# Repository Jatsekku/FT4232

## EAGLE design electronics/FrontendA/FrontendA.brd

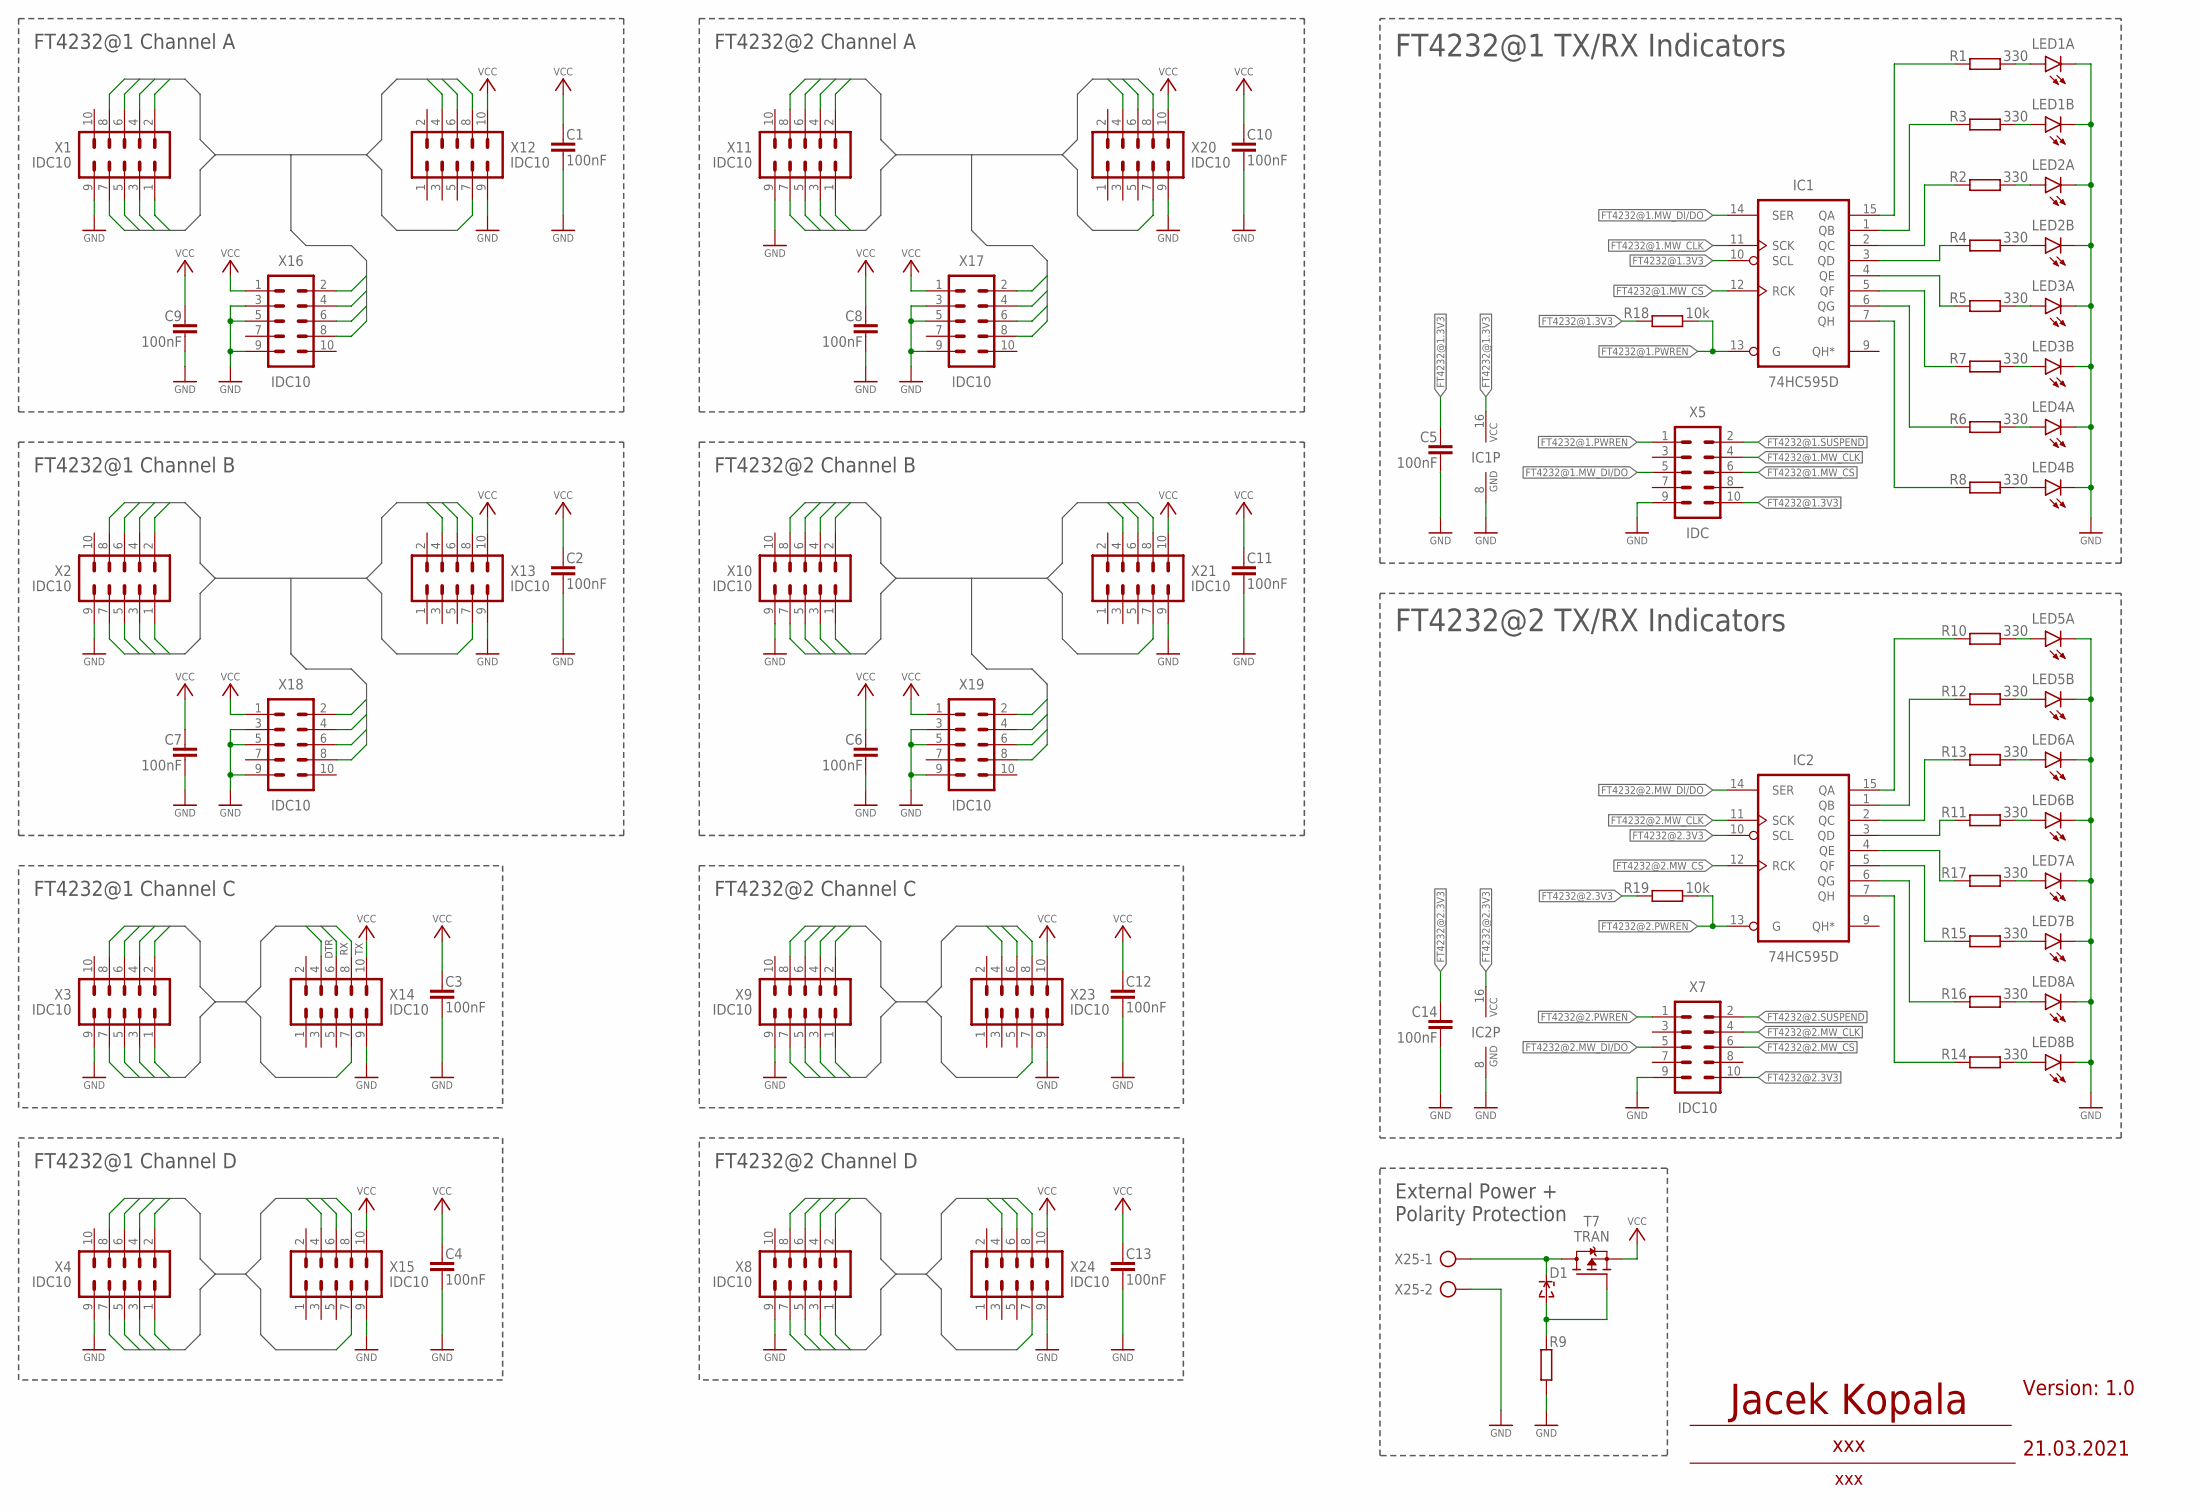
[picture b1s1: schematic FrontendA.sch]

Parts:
C1, C2, C3, C4, C5, C6, C7, C8, C9, C10, C11, C12, C13, C14: 100nF; C0805
D1: ZENERSOD-323F; SOD-323F
IC1, IC2: 74HC595D; SO16
LED1, LED2, LED3, LED4, LED5, LED6, LED7, LED8: LSG-T676; WL-SFCW-0603
R1, R2, R3, R4, R5, R6, R7, R8, R10, R11, R12, R13, R14, R15, R16, R17: 330; R0805
R9: R-EU_R0805; R0805
R18, R19: 10k; R0805
T7: TRAN; TO252
X1, X2, X3, X4, X7, X8, X9, X10, X11: IDC10; MA05-2
X5: IDC; MA05-2
X12, X13, X14, X15, X16, X17, X18, X19, X20, X21, X23, X24: IDC10; ML10
X25: AK500/2

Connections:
FT4232@1.3V3: C5.1, IC1.10 (SCL), IC1.16 (VCC), R18.2, X5.10
FT4232@1.AD0: X1.1, X12.8, X16.4
FT4232@1.AD1: X1.2, X12.6, X16.8
FT4232@1.AD2: X1.3, X12.7, X16.6
FT4232@1.AD3: X1.4, X16.2
FT4232@1.AD4: X1.5, X12.4
FT4232@1.AD5: X1.6
FT4232@1.AD6: X1.7
FT4232@1.AD7: X1.8
FT4232@1.BD0: X2.1, X13.8, X18.4
FT4232@1.BD1: X2.2, X13.6, X18.8
FT4232@1.BD2: X2.3, X13.7, X18.6
FT4232@1.BD3: X2.4, X18.2
FT4232@1.BD4: X2.5, X13.4
FT4232@1.BD5: X2.6
FT4232@1.BD6: X2.7
FT4232@1.BD7: X2.8
FT4232@1.CD0: X3.1, X14.8
FT4232@1.CD1: X3.2, X14.6
FT4232@1.CD2: X3.3, X14.7
FT4232@1.CD3: X3.4
FT4232@1.CD4: X3.5, X14.4
FT4232@1.CD5: X3.6
FT4232@1.CD6: X3.7
FT4232@1.CD7: X3.8
FT4232@1.DD0: X4.1, X15.8
FT4232@1.DD1: X4.2, X15.6
FT4232@1.DD2: X4.3, X15.7
FT4232@1.DD3: X4.4
FT4232@1.DD4: X4.5, X15.4
FT4232@1.DD5: X4.6
FT4232@1.DD6: X4.7
FT4232@1.DD7: X4.8
FT4232@1.MW_CLK: IC1.11 (SCK), X5.4
FT4232@1.MW_CS: IC1.12 (RCK), X5.6
FT4232@1.MW_DI/DO: IC1.14 (SER), X5.5
FT4232@1.PWREN: IC1.13 (G), R18.1, X5.1
FT4232@1.SUSPEND: X5.2
FT4232@2.3V3: C14.1, IC2.10 (SCL), IC2.16 (VCC), R19.2, X7.10
FT4232@2.AD0: X11.1, X17.4, X20.8
FT4232@2.AD1: X11.2, X17.8, X20.6
FT4232@2.AD2: X11.3, X17.6, X20.7
FT4232@2.AD3: X11.4, X17.2
FT4232@2.AD4: X11.5, X20.4
FT4232@2.AD5: X11.6
FT4232@2.AD6: X11.7
FT4232@2.AD7: X11.8
FT4232@2.BD0: X10.1, X19.4, X21.8
FT4232@2.BD1: X10.2, X19.8, X21.6
FT4232@2.BD2: X10.3, X19.6, X21.7
FT4232@2.BD3: X10.4, X19.2
FT4232@2.BD4: X10.5, X21.4
FT4232@2.BD5: X10.6
FT4232@2.BD6: X10.7
FT4232@2.BD7: X10.8
FT4232@2.CD0: X9.1, X23.8
FT4232@2.CD1: X9.2, X23.6
FT4232@2.CD2: X9.3, X23.7
FT4232@2.CD3: X9.4
FT4232@2.CD4: X9.5, X23.4
FT4232@2.CD5: X9.6
FT4232@2.CD6: X9.7
FT4232@2.CD7: X9.8
FT4232@2.DD0: X8.1, X24.8
FT4232@2.DD1: X8.2, X24.6
FT4232@2.DD2: X8.3, X24.7
FT4232@2.DD3: X8.4
FT4232@2.DD4: X8.5, X24.4
FT4232@2.DD5: X8.6
FT4232@2.DD6: X8.7
FT4232@2.DD7: X8.8
FT4232@2.MW_CLK: IC2.11 (SCK), X7.4
FT4232@2.MW_CS: IC2.12 (RCK), X7.6
FT4232@2.MW_DI/DO: IC2.14 (SER), X7.5
FT4232@2.PWREN: IC2.13 (G), R19.1, X7.1
FT4232@2.SUSPEND: X7.2
GND: C1.2, C2.2, C3.2, C4.2, C5.2, C6.2, C7.2, C8.2, C9.2, C10.2, C11.2, C12.2, C13.2, C14.2, IC1.8 (GND), IC2.8 (GND), LED1.P$1 (C), LED1.P$3 (C), LED2.P$1 (C), LED2.P$3 (C), LED3.P$1 (C), LED3.P$3 (C), LED4.P$1 (C), LED4.P$3 (C), LED5.P$1 (C), LED5.P$3 (C), LED6.P$1 (C), LED6.P$3 (C), LED7.P$1 (C), LED7.P$3 (C), LED8.P$1 (C), LED8.P$3 (C), R9.1, X1.9, X2.9, X3.9, X4.9, X5.9, X7.9, X8.9, X9.9, X10.9, X11.9, X12.9, X13.9, X14.9, X15.9, X16.3, X16.5, X16.9, X17.3, X17.5, X17.9, X18.3, X18.5, X18.9, X19.3, X19.5, X19.9, X20.9, X21.9, X23.9, X24.9, X25.2
unnamed: LED1.P$2 (A), R1.2
unnamed: LED1.P$4 (A), R3.2
unnamed: LED5.P$2 (A), R10.2
unnamed: LED5.P$4 (A), R12.2
unnamed: LED2.P$2 (A), R2.2
unnamed: LED2.P$4 (A), R4.2
unnamed: LED3.P$2 (A), R5.2
unnamed: LED6.P$2 (A), R13.2
unnamed: LED3.P$4 (A), R7.2
unnamed: LED6.P$4 (A), R11.2
unnamed: LED4.P$2 (A), R6.2
unnamed: LED4.P$4 (A), R8.2
unnamed: IC1.3 (QD), R4.1
unnamed: IC1.4 (QE), R5.1
unnamed: IC1.2 (QC), R2.1
unnamed: IC1.1 (QB), R3.1
unnamed: IC1.15 (QA), R1.1
unnamed: IC1.5 (QF), R7.1
unnamed: IC1.6 (QG), R6.1
unnamed: IC1.7 (QH), R8.1
unnamed: LED7.P$2 (A), R17.2
unnamed: LED7.P$4 (A), R15.2
unnamed: LED8.P$2 (A), R16.2
unnamed: LED8.P$4 (A), R14.2
unnamed: IC2.3 (QD), R11.1
unnamed: IC2.4 (QE), R17.1
unnamed: IC2.2 (QC), R13.1
unnamed: IC2.1 (QB), R12.1
unnamed: IC2.15 (QA), R10.1
unnamed: IC2.5 (QF), R15.1
unnamed: IC2.6 (QG), R16.1
unnamed: IC2.7 (QH), R14.1
unnamed: D1.A, R9.2, T7.1 (G)
VCC: C1.1, C2.1, C3.1, C4.1, C6.1, C7.1, C8.1, C9.1, C10.1, C11.1, C12.1, C13.1, T7.2 (S), X12.10, X13.10, X14.10, X15.10, X16.1, X17.1, X18.1, X19.1, X20.10, X21.10, X23.10, X24.10
VIN: D1.C, T7.3 (D), X25.1

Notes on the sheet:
DTR
FT4232@1 Channel A
FT4232@2 Channel A
FT4232@1 Channel B
FT4232@2 Channel B
FT4232@1 Channel C
FT4232@1 Channel D
FT4232@2 Channel C
FT4232@2 Channel D
FT4232@2 TX/RX Indicators
FT4232@1 TX/RX Indicators
External Power + Polarity Protection
21.03.2021
Version: 1.0
Jacek Kopala
xxx

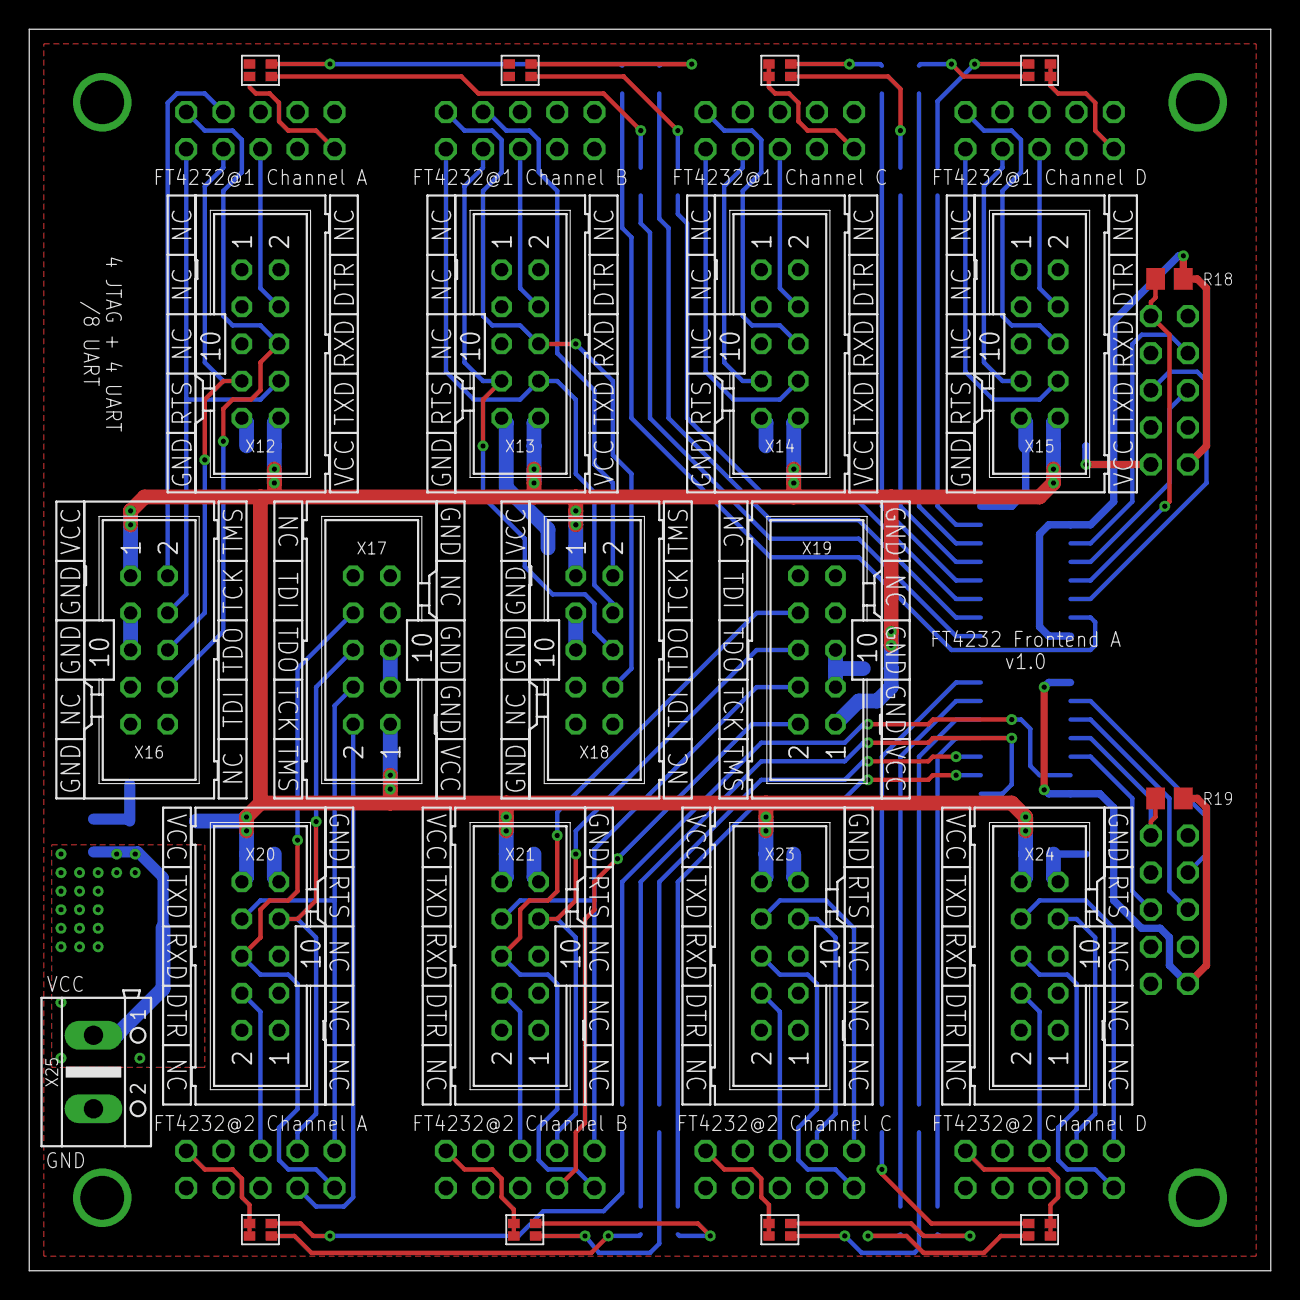
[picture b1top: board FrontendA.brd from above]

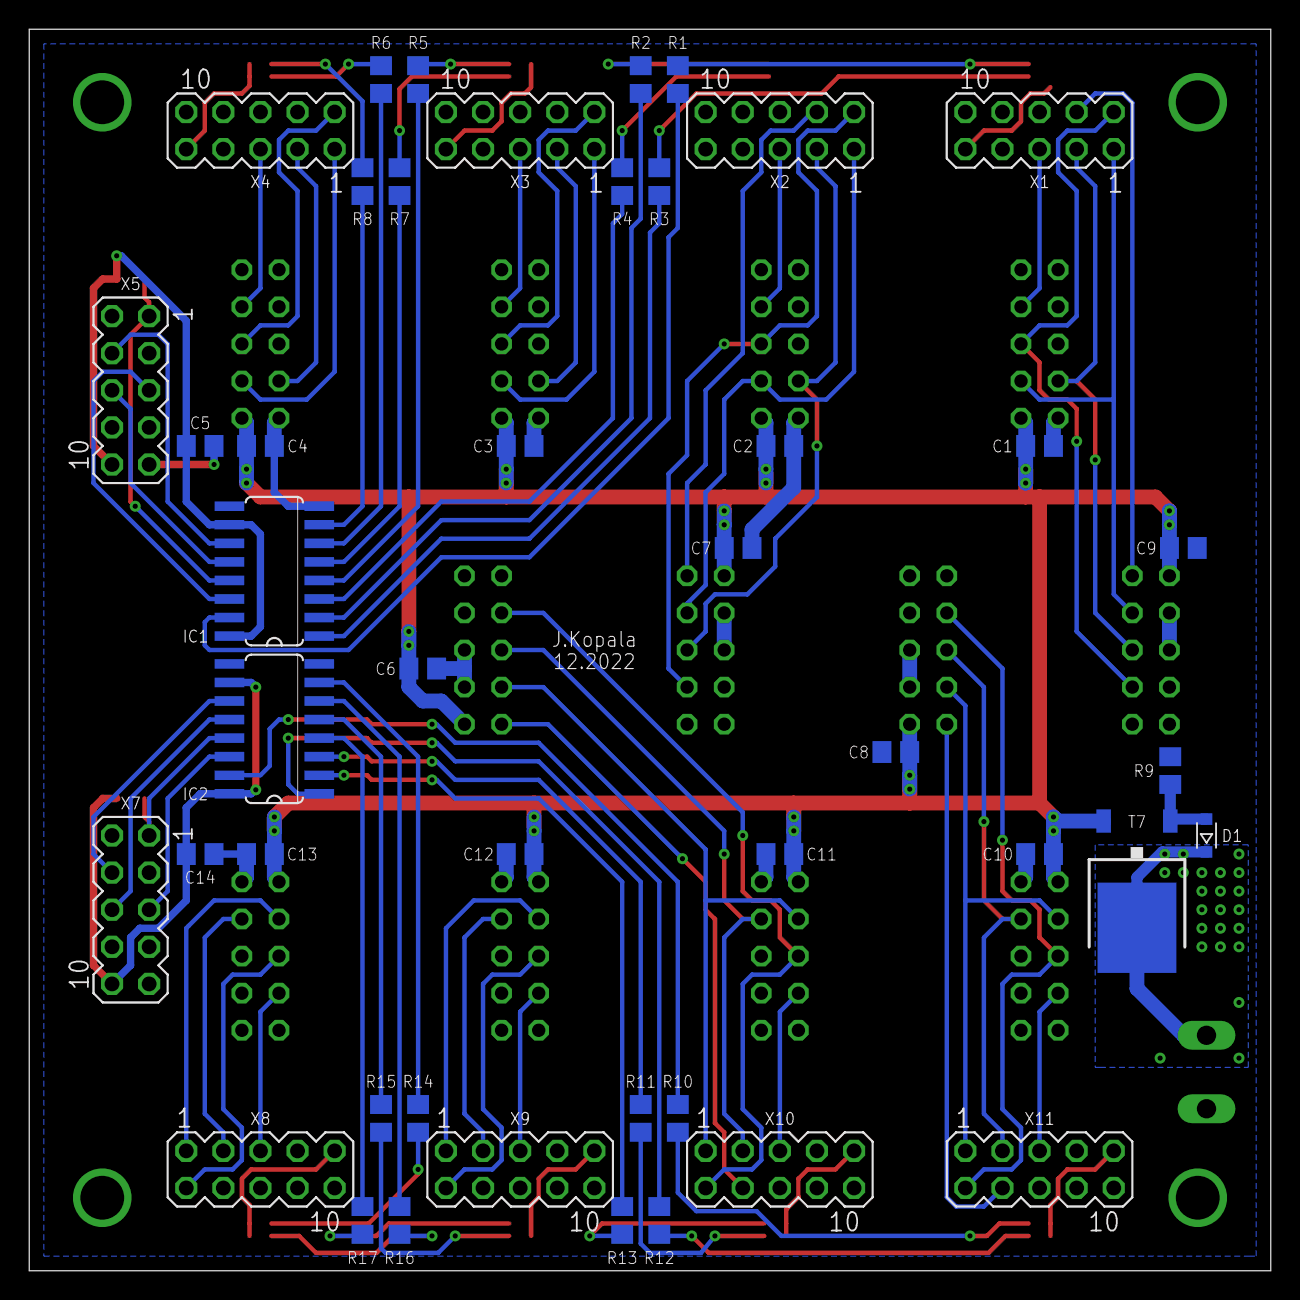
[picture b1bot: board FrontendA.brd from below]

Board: 2 copper layers, 85.0 x 85.0 mm, 68 parts (35 on the bottom side), 82 nets.

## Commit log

2022-11-30 electronics/FrontendA: Add frontend design
    This commit introduces full design of Frontend "A".
    It contains Eagle 's .sch and .brd files.
    Schematic has also been exported as .pdf file.
